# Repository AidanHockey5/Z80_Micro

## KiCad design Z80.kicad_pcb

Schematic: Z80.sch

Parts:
BAR1: DATA; HDSP-4830
BAR2: ADDR_TOP; HDSP-4830
BAR3: ADDR_BTM; HDSP-4830
C1, C4, C5, C6, C7, C8, C11, C12: 100nF; C_Disc_D3.0mm_W1.6mm_P2.50mm
C2, C3, C9, C10: 22pF; C_Disc_D3.0mm_W1.6mm_P2.50mm
J1: USB_B
J2: Conn_01x16_Male; Pin_Header_Straight_1x16_Pitch2.54mm
J3: Conn_01x08_Male; Pin_Header_Straight_1x08_Pitch2.54mm
J4: Conn_01x02_Male; Pin_Header_Straight_1x02_Pitch2.54mm
R1: 1M; R_Axial_DIN0207_L6.3mm_D2.5mm_P7.62mm_Horizontal
R2: 1K; R_Axial_DIN0207_L6.3mm_D2.5mm_P7.62mm_Horizontal
R3: 3k3; R_Axial_DIN0207_L6.3mm_D2.5mm_P7.62mm_Horizontal
R4: 2k2; R_Axial_DIN0207_L6.3mm_D2.5mm_P7.62mm_Horizontal
RN1, RN2, RN3: 1k; R_Array_SIP9
SW1: SW_Push_Dual; SW_TH_Tactile_Omron_B3F-10xx
U1: 74HCT04; DIP-14_W7.62mm
U2: 68B50; DIP-24_W15.24mm
U3: Z80CPU; DIP-40_W15.24mm
U4: 2764; DIP-28_W15.24mm
U5: 628128; DIP-32_W15.24mm
U6: 74LS32; DIP-14_W7.62mm
U7: CH340G; SOIC16
Y1: 7.3728MHz; Crystal_HC49-U_Vertical
Y2: 12MHz; Crystal_HC49-U_Vertical

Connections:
A0: BAR3.1, J2.1, U2.11, U3.30, U4.10 (A0), U5.12
A1: BAR3.2, J2.2, U3.31, U4.9 (A1), U5.11
A2: BAR3.3, J2.3, U3.32, U4.8 (A2), U5.10
A3: BAR3.4, J2.4, U3.33, U4.7 (A3), U5.9
A4: BAR3.5, J2.5, U3.34, U4.6 (A4), U5.8
A5: BAR3.6, J2.6, U3.35, U4.5 (A5), U5.7
A6: BAR3.7, J2.7, U2.9, U3.36, U4.4 (A6), U5.6
A7: BAR3.8, J2.8, U2.10, U3.37, U4.3 (A7), U5.5
A8: BAR3.9, J2.9, U3.38, U4.25 (A8), U5.27
A9: BAR3.10, J2.10, U3.39, U4.24 (A9), U5.26
A10: BAR2.1, J2.11, U3.40, U4.21 (A10), U5.23
A11: BAR2.2, J2.12, U3.1, U4.23 (A11), U5.25
A12: BAR2.3, J2.13, U3.2, U4.2 (A12), U5.4
A13: BAR2.4, J2.14, U3.3, U5.28, U6.1
A14: BAR2.5, J2.15, U3.4, U5.3, U6.2
A15: BAR2.6, J2.16, U3.5, U5.31, U6.13
CTS: U2.5, U7.9
D0: BAR1.1, J3.1, U2.22, U3.14, U4.11 (D0), U5.13
D1: BAR1.2, J3.2, U2.21, U3.15, U4.12 (D1), U5.14
D2: BAR1.3, J3.3, U2.20, U3.12, U4.13 (D2), U5.15
D3: BAR1.4, J3.4, U2.19, U3.8, U4.15 (D3), U5.17
D4: BAR1.5, J3.5, U2.18, U3.7, U4.16 (D4), U5.18
D5: BAR1.6, J3.6, U2.17, U3.9, U4.17 (D5), U5.19
D6: BAR1.7, J3.7, U2.16, U3.10, U4.18 (D6), U5.20
D7: BAR1.8, J3.8, U2.15, U3.13, U4.19 (D7), U5.21
GND: BAR1.9, BAR1.10, BAR1.11, BAR1.12, BAR2.7, BAR2.8, BAR2.9, BAR2.10, BAR2.11, BAR2.12, BAR2.13, BAR2.14, C1.1, C2.2, C3.2, C4.2, C5.2, C6.2, C7.2, C8.2, C9.2, C10.2, C11.2, C12.1, J1.4, RN1.1, RN2.1, RN3.1, U1.7, U2.1, U2.23, U2.24, U3.29, U4.14 (GND), U5.2, U5.16, U5.22, U6.7, U7.1; also elsewhere on the board
INT: R3.2, U2.7, U3.16
IORQ: U1.5, U3.20
M1: U2.8, U3.27
MREQ: U3.19, U6.5, U6.9
M_CLK: U1.4, U2.3, U2.4, U3.6
unnamed: BAR1.13, RN1.9
unnamed: BAR1.14, RN1.8
unnamed: BAR1.15, RN1.7
unnamed: BAR1.16, RN1.6
unnamed: BAR1.17, RN1.5
unnamed: BAR1.18, RN1.4
unnamed: BAR1.19, RN1.3
unnamed: BAR1.20, RN1.2
unnamed: BAR2.15, RN2.9
unnamed: BAR2.16, RN2.8
unnamed: BAR2.17, RN2.7
unnamed: BAR2.18, RN2.6
unnamed: BAR2.19, RN2.5
unnamed: BAR2.20, RN2.4
unnamed: BAR3.11, RN2.3
unnamed: BAR3.12, RN2.2
unnamed: BAR3.13, RN3.9
unnamed: BAR3.14, RN3.8
unnamed: BAR3.15, RN3.7
unnamed: BAR3.16, RN3.6
unnamed: BAR3.17, RN3.5
unnamed: BAR3.18, RN3.4
unnamed: BAR3.19, RN3.3
unnamed: BAR3.20, RN3.2
unnamed: C2.1, R1.2, U1.1, Y1.1
unnamed: C3.1, R2.2, Y1.2
unnamed: C9.1, U7.7, Y2.1
unnamed: C10.1, U7.8, Y2.2
unnamed: C11.1, U7.4
unnamed: J1.2, U7.6
unnamed: J1.3, U7.5
unnamed: R1.1, R2.1, U1.2, U1.3
unnamed 64: R4.2, U3.26; also elsewhere on the board
unnamed: U1.6, U2.14
unnamed: U4.20 (CE), U5.30, U6.11
unnamed: U4.22 (OE), U5.24, U6.8
unnamed: U5.29, U6.6
unnamed: U6.3, U6.12
RD: U3.21, U6.10
RXD: U2.2, U7.2
TXD: U2.6, U7.3
WR: U2.13, U3.22, U6.4

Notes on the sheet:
Z80 Prototype
Wednesday, September 19 2018

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
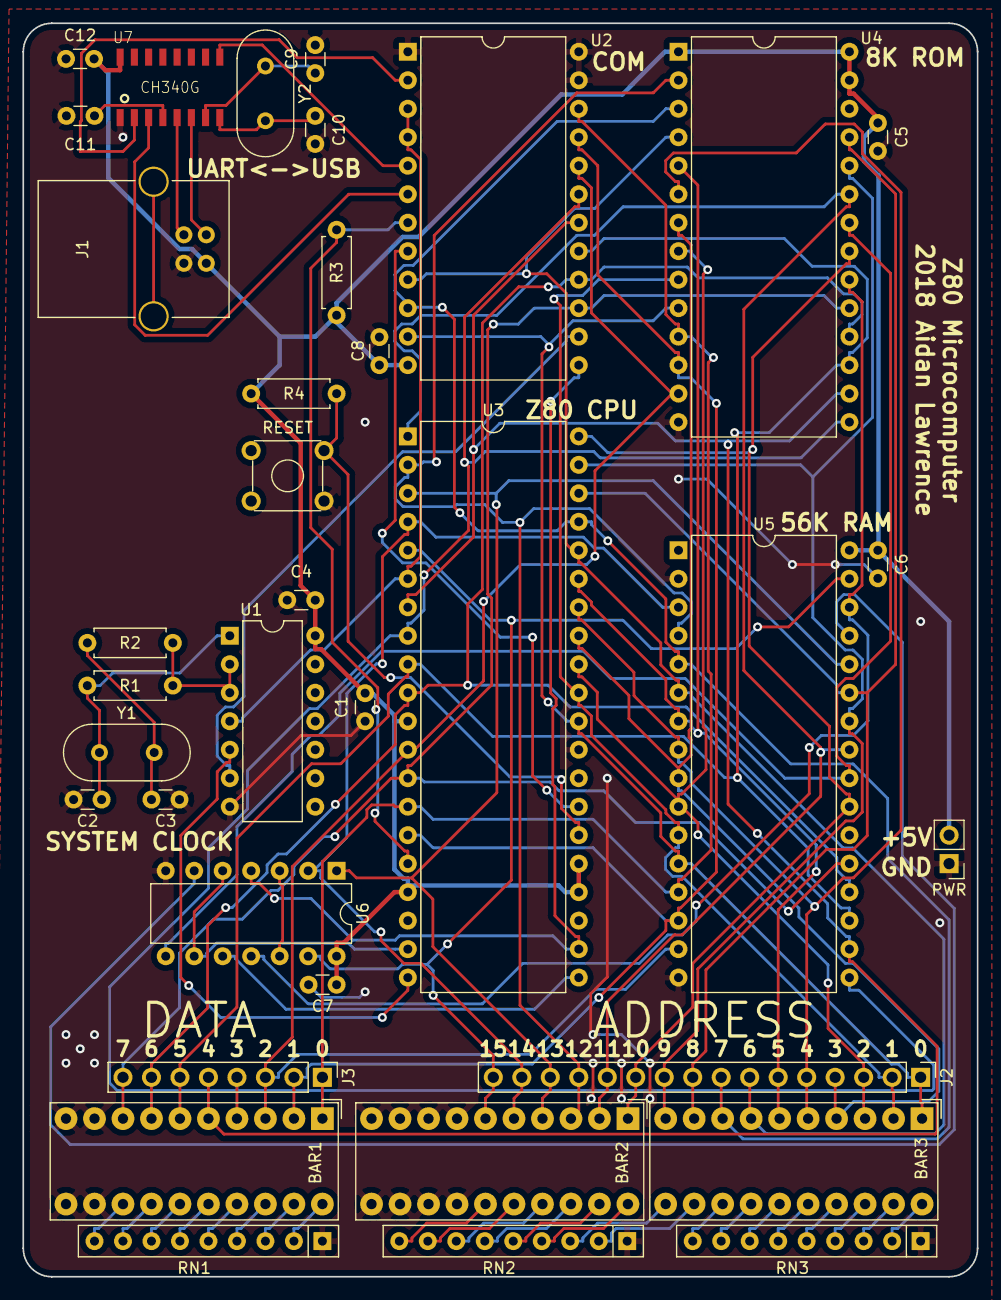
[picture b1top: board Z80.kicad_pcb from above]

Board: 2 copper layers, 85.1 x 111.8 mm, 38 parts (1 on the bottom side), 74 nets.

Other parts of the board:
G01: LOGO; z80_Logo1
G02: LOGO; z80_Logo2
PWR: Conn_01x02_Male; Pin_Header_Straight_1x02_Pitch2.54mm
RESET: SW_Push_Dual; SW_TH_Tactile_Omron_B3F-10xx

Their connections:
GND: PWR.1, RESET.4; also elsewhere on the board
unnamed 64: RESET.2; also elsewhere on the board

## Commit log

2018-09-21 Z80 board done. Init repo
2018-10-01 Send to github
2018-10-01 Added schematic plots
2018-10-01 Update symbols
2018-10-01 lib files added
